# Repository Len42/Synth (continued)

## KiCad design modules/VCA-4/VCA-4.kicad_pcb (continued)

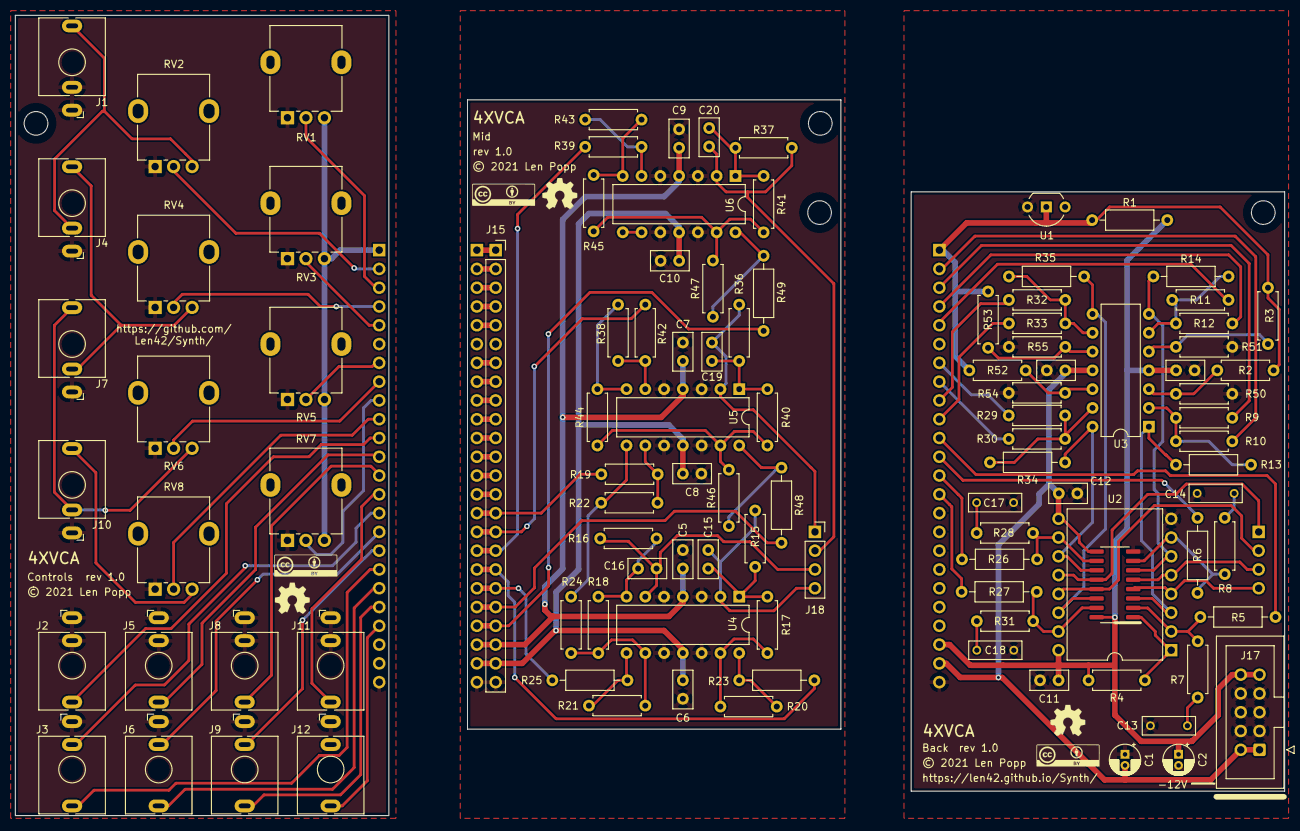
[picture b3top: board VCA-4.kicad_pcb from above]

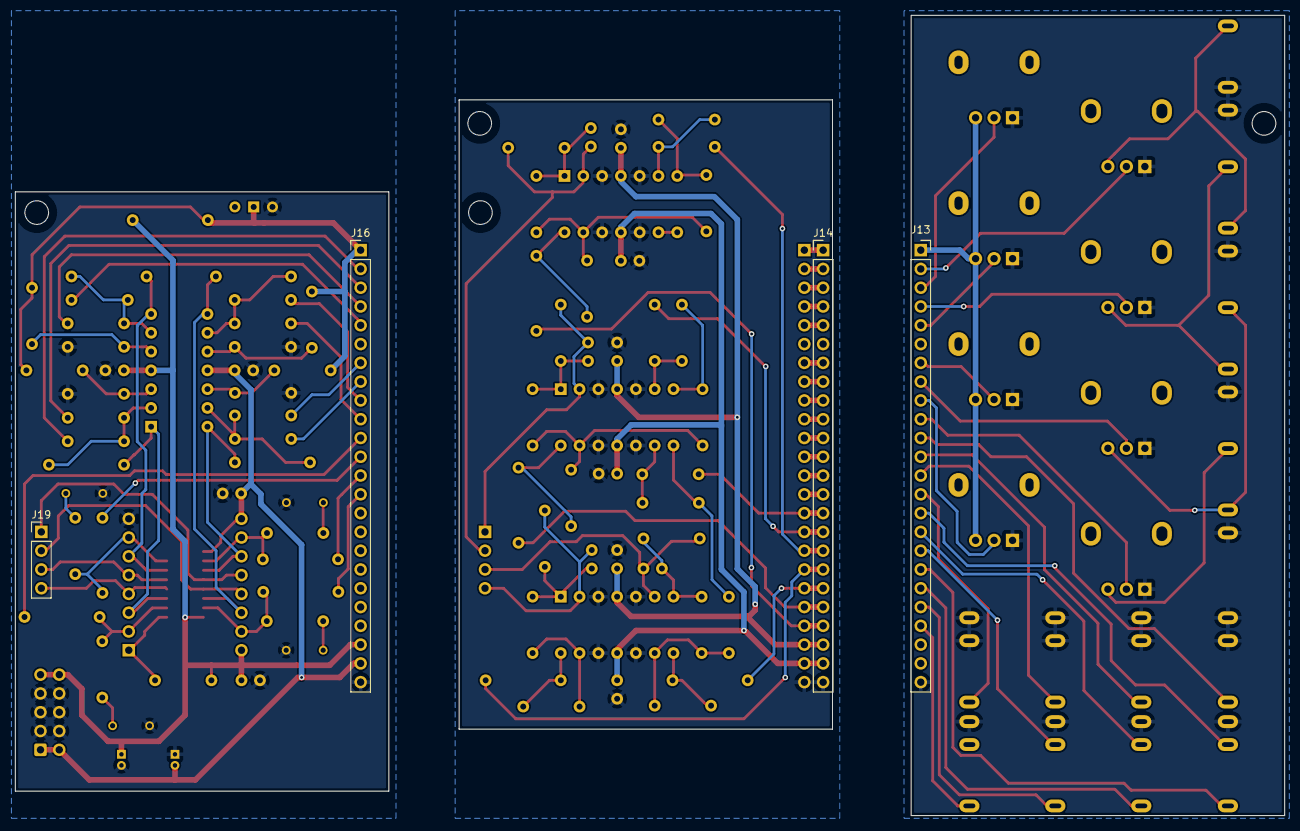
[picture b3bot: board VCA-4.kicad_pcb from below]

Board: 2 copper layers, 171.6 x 108.2 mm, 118 parts (4 on the bottom side), 71 nets.

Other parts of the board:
G2, G2#2, G2#3: Logo_CC_BY
G4, G4#2, G4#3: Logo_OSHW

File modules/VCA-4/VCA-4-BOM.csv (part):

Ref,Qty,Value,Value2,Note,Description,Datasheet,Manufacturer,ManuPartNum,Distributor1,DistributorPartNum1,DistributorPartLink1,Distributor2,DistributorPartNum2,DistributorPartLink2,Distributor3,DistributorPartNum3,DistributorPartLink3
"A1","1","Cable_Eurorack_10","","Length as required","Eurorack 16-10 pin power cable","","","","Thonk","","https://www.thonk.co.uk/shop/eurorack-power-cables/","SynthCube","","https://synthcube.com/cart/eurorack-ribbon-power-cables","Modular Addict","","https://modularaddict.com/parts/eurorack-power-cables-1"
"C1 C2","2","10U","25 VDC","12 V decoupling","Capacitor - Electrolytic - 12 V decoupling","https://industrial.panasonic.com/cdbs/www-data/pdf/RDF0000/A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","Panasonic","EEA-FC1E100","Mouser","667-EEA-FC1E100","https://www.mouser.ca/ProductDetail/Panasonic/EEA-FC1E100?qs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","","","","","",""
"C3 C4 C5 C6 C7 C8 C9 C10 C11 C12","10","100N","","IC decoupling","Capacitor - Ceramic - IC decoupling","https://product.tdk.com/system/files/dam/doc/product/capacit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","TDK","FG18X7R1H104KNT06","Mouser","810-FG18X7R1H104KNT6","https://www.mouser.ca/ProductDetail/810-FG18X7R1H104KNT6","","","","","",""
"C13 C14 C17 C18","4","1N2","","C0G or film","Capacitor - Ceramic","https://www.mouser.ca/datasheet/2/212/1/KEM_F3101_R82-1103738.pdf","Kemet","R82EC1120DQ50J","Mouser","80-R82EC1120DQ50J","https://www.mouser.ca/ProductDetail/KEMET/R82EC1120DQ50J?qs=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","","","","","",""
"C15 C16 C19 C20","4","100P","","","Capacitor - Ceramic","https://www.mouser.ca/datasheet/2/427/VISH_S_A0012659393_1-2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","Vishay","K101J15C0GF53L2","Mouser","594-K101J15C0GF53L2","https://www.mouser.ca/ProductDetail/594-K101J15C0GF53L2","","","","","",""
"H1 H5 H6 H10","4","Screw_M3x0.50x6","","","Machine screw, M3x0.50x6","","","","","","","","","","","",""
"H3 H8","2","Standoff_F-F_11mm_M3x0.50","","","Standoff, 11mm, female-female, M3x0.50","https://www.thonk.co.uk/wp-content/uploads/2018/05/standoff-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","Ettinger","05.03.111","Thonk","Mech_11mm_Standoff_(x10)","https://www.thonk.co.uk/shop/standoffs/","Mouser","710-970110321","https://www.mouser.ca/ProductDetail/Wurth-Elektronik/9701103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","","",""
"J1 J2 J3 J4 J5 J6 J7 J8 J9 J10 J11 J12","12","WQP-PJ398","","","Audio Jack, 2 Poles (Mono / TS), Switched T Pole (Normalling), QingPu / Thonkiconn","http://www.qingpu-electronics.com/en/products/WQP-PJ398SM-362.html","QingPu / Thonk","PJ398SM / WQP518MA","Thonk","PJ398SM","https://www.thonk.co.uk/shop/thonkiconn/","SynthCube","WQP518MA","https://synthcube.com/cart/3-5mm-euro-jacks","Adafruit","4031","https://www.adafruit.com/product/4031"
"J13 J15","2","Conn_Socket_24","","","Generic connector, single row, 01x24, script generated (kicad-library-utils/schlib/autogen/connector/)","https://www.mouser.ca/datasheet/2/445/61303211821-1717799.pdf","","","Adafruit","598","https://www.adafruit.com/product/598","Mouser","710-61303211821","https://www.mouser.ca/ProductDetail/Wurth-Elektronik/6130321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","","",""
"J14 J16","2","Conn_Header_24","","","Generic connector, single row, 01x24, script generated (kicad-library-utils/schlib/autogen/connector/)","https://www.amphenol-icc.com/media/wysiwyg/files/documentati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","","","Adafruit","392","https://www.adafruit.com/product/392","Mouser","649-1012937893601BLF","https://www.mouser.ca/ProductDetail/649-1012937893601BLF","","",""
"J17","1","Conn_Eurorack_10","","","Eurorack 10-pin board power connector","https://www.mouser.ca/datasheet/2/445/61201021621-1717731.pdf","Wurth Elektronik","61201021621","Mouser","710-61201021621","https://www.mouser.ca/ProductDetail/Wurth-Elektronik/6120102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","Mouser","523-G821EU210AAL10Y","https://www.mouser.ca/ProductDetail/523-G821EU210AAL10Y","","",""
"J18","1","Conn_Socket_4","","","Generic connector, single row, 01x04, script generated (kicad-library-utils/schlib/autogen/connector/)","https://www.mouser.ca/datasheet/2/445/61303211821-1717799.pdf","","","Adafruit","598","https://www.adafruit.com/product/598","Mouser","710-61303211821","https://www.mouser.ca/ProductDetail/Wurth-Elektronik/6130321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","","",""
"J19","1","Conn_Header_4","","","Generic connector, single row, 01x04, script generated (kicad-library-utils/schlib/autogen/connector/)","https://www.amphenol-icc.com/media/wysiwyg/files/documentati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","","","Adafruit","392","https://www.adafruit.com/product/392","Mouser","649-1012937893601BLF","https://www.mouser.ca/ProductDetail/649-1012937893601BLF","","",""
"R1 R23 R25 R48 R49","5","1K","5%, 1/4 W","Output limiting","Resistor","https://www.mouser.ca/datasheet/2/427/ccf07-1762725.pdf","Vishay / Dale","CCF071K00JKE36","Mouser","71-CCF071K00JKE36","https://www.mouser.ca/ProductDetail/Vishay-Dale/CCF071K00JKE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","","","","","",""
"R2 R3 R52 R53","4","25K5","1%, 1/6 W","","Resistor","https://www.mouser.ca/datasheet/2/447/Yageo_LR_MFR_1-1714151.pdf","YAGEO","MFR-25FRF52-25K5","Mouser","603-MFR-25FRF52-25K5","https://www.mouser.ca/ProductDetail/603-MFR-25FRF52-25K5","","","","","",""
"R4","1","12K","1%, 1/6 W","","Resistor","https://www.mouser.ca/datasheet/2/447/Yageo_LR_MFR_1-1714151.pdf","YAGEO","MFR-12FTF52-12K","Mouser","603-MFR-12FTF52-12K","https://www.mouser.ca/ProductDetail/603-MFR-12FTF52-12K","","","","","",""
"R5 R6 R26 R27","4","49K9","","","Resistor","https://www.mouser.ca/datasheet/2/427/cmfmil-1762972.pdf","Vishay / Dale","RN55D4992FB14","Mouser","71-RN55D-F-49.9K","https://www.mouser.ca/ProductDetail/?qs=Bfn3yGQ%252BnqpBsi5J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","","","","","",""
"R7 R8 R28 R31","4","220R","1%, 1/6 W","","Resistor","https://www.mouser.ca/datasheet/2/447/Yageo_LR_MFR_1-1714151.pdf","YAGEO","MFR-12FTF52-220R","Mouser"," 603-MFR-12FTF52-220R","https://www.mouser.ca/ProductDetail/603-MFR-12FTF52-220R","","","","","",""
"R9 R11 R29 R32","4","75K","1%, 1/6 W","","Resistor","https://www.mouser.ca/datasheet/2/447/Yageo_LR_MFR_1-1714151.pdf","YAGEO","MFR-12FTF52-75K","Mouser","603-MFR-12FTF52-75K","https://www.mouser.ca/ProductDetail/YAGEO/MFR-12FTF52-75K?qs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","","","","","",""
"R10 R12 R30 R33","4","150K","1%, 1/6 W","","Resistor","https://www.mouser.ca/datasheet/2/447/Yageo_LR_MFR_1-1714151.pdf","YAGEO","MFR-12FTF52-150K","Mouser","603-MFR-12FTF52-150K","https://www.mouser.ca/ProductDetail/YAGEO/MFR-12FTF52-150K?q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","","","","","",""
"R13 R14 R34 R35","4","60K1","1%","","Resistor","https://www.mouser.ca/datasheet/2/427/cmfmil-1762972.pdf","Vishay / Dale","RN55D6012FB14","Mouser","71-RN55D-F-60.1K","https://www.mouser.ca/ProductDetail/71-RN55D-F-60.1K","","","","","",""
"R15 R16 R36 R37","4","20K","1%, 1/6 W","","Resistor","https://www.mouser.ca/datasheet/2/447/Yageo_LR_MFR_1-1714151.pdf","YAGEO","MFR-12FTF52-20K","Mouser","603-MFR-12FTF52-20K","https://www.mouser.ca/ProductDetail/YAGEO/MFR-12FTF52-20K?qs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","","","","","",""
"R17 R18 R19 R20 R21 R22 R24 R38 R39 R40 R41 R42 R43 R44 R45 R46 R47","17","47K","1%, 1/6 W","","Resistor","https://www.mouser.ca/datasheet/2/447/Yageo_LR_MFR_1-1714151.pdf","YAGEO","MFR-12FTF52-47K","Mouser","603-MFR-12FTF52-47K","https://www.mouser.ca/ProductDetail/YAGEO/MFR-12FTF52-47K?qs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","","","","","",""
"R50 R51 R54 R55","4","11K","1%, 1/6 W","","Resistor","https://www.mouser.ca/datasheet/2/447/Yageo_LR_MFR_1-1714151.pdf","YAGEO","MFR-12FTF52-11K","Mouser","603-MFR-12FTF52-11K","https://www.mouser.ca/ProductDetail/YAGEO/MFR-12FTF52-11K?qs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","","","","","",""
"RV1 RV3 RV5 RV7","4","100K","LIN","","Potentiometer","https://www.mouser.ca/datasheet/2/13/alpha_taiwan_08192019_R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","Alpha","RD901F-40-15R1-B100K-00DL1","Thonk","Group_Pot_Alpha_6.35mm","https://www.thonk.co.uk/shop/alpha-9mm-pots/","Mouser","311-1940F-15R1-B100K","https://www.mouser.ca/ProductDetail/Alpha-Taiwan/RD901F-40-1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","SynthCube","9MMALPHAPOTMSTR","https://synthcube.com/cart/alpha-9mm-potentiometer-right-ang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"
"RV2 RV4 RV6 RV8","4","100K","LIN","","Potentiometer","http://www.song-huei.com/proimages//eng/pdfimages/R0904N.pdf","Song Huei","R0904N*","SynthCube","SH9MMTPOTMSTR","https://synthcube.com/cart/9mm-trimmer-pots","Thonk","Group_SongHuei_TTP","https://www.thonk.co.uk/shop/ttpots/","","",""
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
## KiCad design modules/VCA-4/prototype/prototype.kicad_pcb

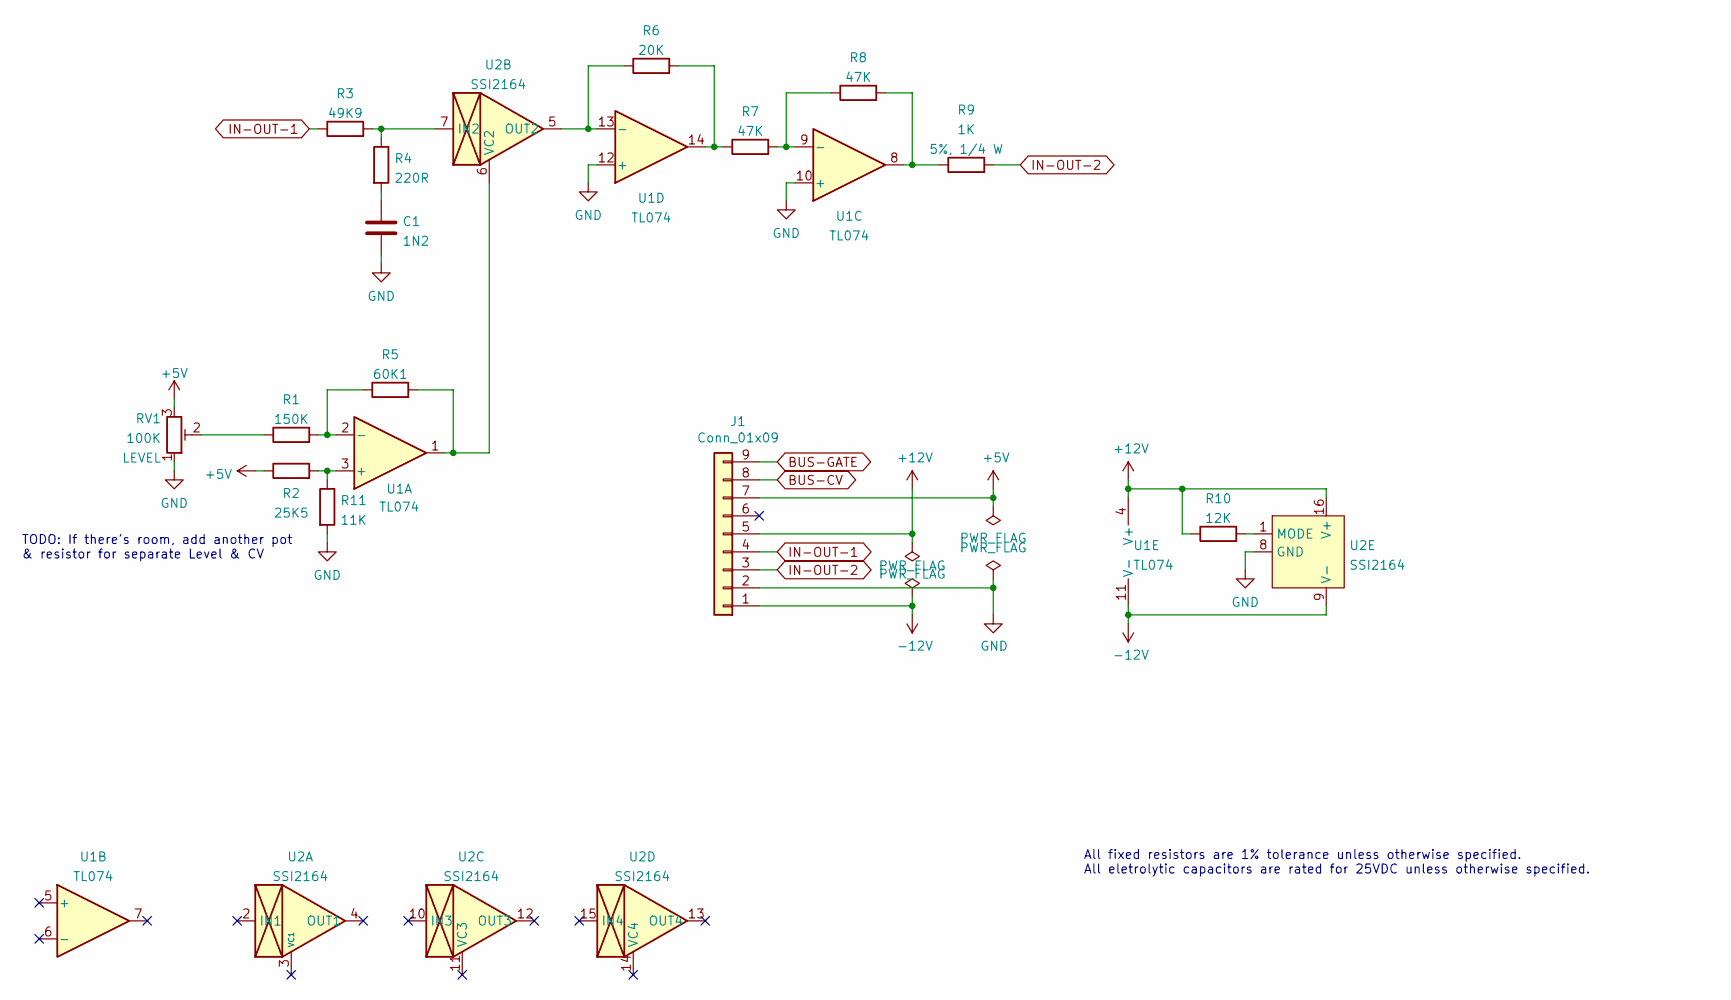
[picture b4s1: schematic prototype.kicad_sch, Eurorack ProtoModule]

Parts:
C1: 1N2; C_Rect_Kemet_L7.2mm_W2.5mm_P5mm
J1: Conn_01x09; PinHeader_1x09_P2.54mm_Vertical
R1: 150K; R_Axial_DIN0207_L6.3mm_D2.5mm_P7.62mm_Horizontal; ManufacturerPartNum MFR-12*
R2: 25K5; R_Axial_DIN0207_L6.3mm_D2.5mm_P7.62mm_Horizontal; ManufacturerPartNum MFR-12*
R3: 49K9; R_Axial_DIN0207_L6.3mm_D2.5mm_P10.16mm_Horizontal; ManufacturerPartNum MFR-12*
R4: 220R; R_Axial_DIN0207_L6.3mm_D2.5mm_P7.62mm_Horizontal; ManufacturerPartNum MFR-12*
R5: 60K1; SB_Gen_1; ManufacturerPartNum MFR-12*
R6: 20K; SB_Gen_1; ManufacturerPartNum MFR-12*
R7: 47K; SB_Gen_5; ManufacturerPartNum MFR-12*
R8: 47K; SB_Gen_1; ManufacturerPartNum MFR-12*
R9: 1K; SB_Gen_1; ManufacturerPartNum CCF071K00JKE36
R10: 12K; R_Axial_DIN0207_L6.3mm_D2.5mm_P7.62mm_Horizontal; ManufacturerPartNum MFR-12*
R11: 11K; SB_Gen_1; ManufacturerPartNum MFR-12*
RV1: 100K; Potentiometer_Bourns_3310R_Top; ManufacturerPartNum 3386*
U1: TL074; DIP-14_W7.62mm; ManufacturerPartNum TL074BCN
U2: SSI2164; Breakout_DIP-16_W15.24mm; ManufacturerPartNum SSI2164

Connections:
+5V: J1.7, R2.1, RV1.3
+12V: J1.5, R10.1, U1.4 (V+), U2.16 (V+)
-12V: J1.1, U1.11 (V-), U2.9 (V-)
BUS-CV: J1.8
BUS-GATE: J1.9
GND: C1.2, J1.2, R11.2, RV1.1, U1.10 (+), U1.12 (+), U2.8 (GND)
IN-OUT-1: J1.4, R3.1
IN-OUT-2: J1.3, R9.2
unnamed: C1.1, R4.2
unnamed: R1.1, RV1.2
unnamed: R1.2, R5.1, U1.2 (-)
unnamed: R3.2, R4.1, U2.7 (IN2)
unnamed: R5.2, U1.1, U2.6 (VC2)
unnamed: R6.1, U1.13 (-), U2.5 (OUT2)
unnamed: R6.2, R7.1, U1.14
unnamed: R7.2, R8.1, U1.9 (-)
unnamed: R8.2, R9.1, U1.8
unnamed: R10.2, U2.1 (MODE)
unnamed: R2.2, R11.1, U1.3 (+)

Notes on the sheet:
TODO: If there's room, add another pot & resistor for separate Level & CV
All fixed resistors are 1% tolerance unless otherwise specified. All eletrolytic capacitors are rated for 25VDC unless otherwise specified.

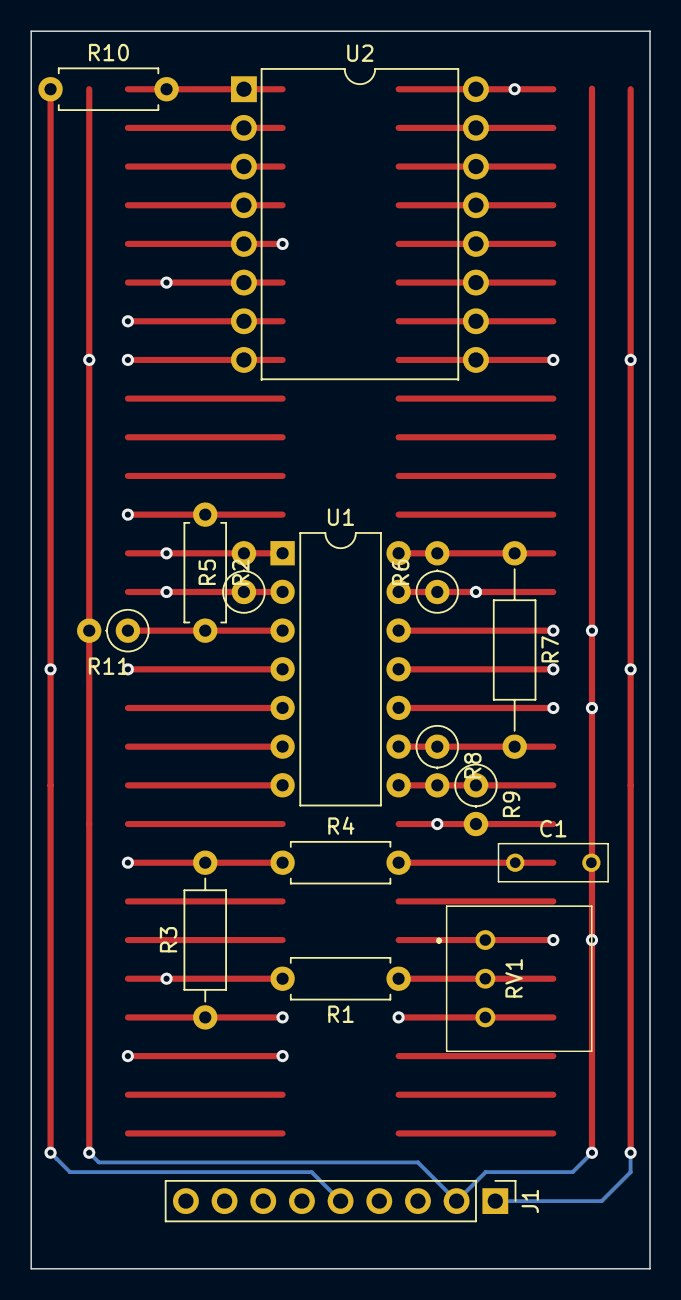
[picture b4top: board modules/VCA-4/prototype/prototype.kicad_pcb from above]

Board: 6 copper layers, 40.6 x 81.3 mm, 16 parts (0 on the bottom side), 17 nets.

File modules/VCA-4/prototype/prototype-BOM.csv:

Ref,Qty,Name,Value,Value2,Note,Description,Datasheet,Manufacturer,ManuPartNum,Distributor1,DistributorPartNum1,DistributorPartLink1,Distributor2,DistributorPartNum2,DistributorPartLink2
"C1","1","CF","1N2","","","Capacitor - Film","","","","","","","","",""
"J1","1","Conn_01x09","Conn_01x09","","","Generic connector, single row, 01x09, script generated (kicad-library-utils/schlib/autogen/connector/)","","","","","","","","",""
"R1","1","R","150K","1%, 1/6 W","","Resistor","https://www.mouser.ca/datasheet/2/447/Yageo_LR_MFR_1-1714151.pdf","YAGEO","MFR-12*","Mouser","603-MFR-12*","https://www.mouser.ca/c/passive-components/resistors/film-re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","","",""
"R2","1","R","25K5","1%, 1/6 W","","Resistor","https://www.mouser.ca/datasheet/2/447/Yageo_LR_MFR_1-1714151.pdf","YAGEO","MFR-12*","Mouser","603-MFR-12*","https://www.mouser.ca/c/passive-components/resistors/film-re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","","",""
"R3","1","R","49K9","1%, 1/6 W","","Resistor","https://www.mouser.ca/datasheet/2/447/Yageo_LR_MFR_1-1714151.pdf","YAGEO","MFR-12*","Mouser","603-MFR-12*","https://www.mouser.ca/c/passive-components/resistors/film-re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","","",""
"R4","1","R","220R","1%, 1/6 W","","Resistor","https://www.mouser.ca/datasheet/2/447/Yageo_LR_MFR_1-1714151.pdf","YAGEO","MFR-12*","Mouser","603-MFR-12*","https://www.mouser.ca/c/passive-components/resistors/film-re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","","",""
"R5","1","R","60K1","1%, 1/6 W","","Resistor","https://www.mouser.ca/datasheet/2/447/Yageo_LR_MFR_1-1714151.pdf","YAGEO","MFR-12*","Mouser","603-MFR-12*","https://www.mouser.ca/c/passive-components/resistors/film-re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","","",""
"R6","1","R","20K","1%, 1/6 W","","Resistor","https://www.mouser.ca/datasheet/2/447/Yageo_LR_MFR_1-1714151.pdf","YAGEO","MFR-12*","Mouser","603-MFR-12*","https://www.mouser.ca/c/passive-components/resistors/film-re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","","",""
"R7 R8","2","R","47K","1%, 1/6 W","","Resistor","https://www.mouser.ca/datasheet/2/447/Yageo_LR_MFR_1-1714151.pdf","YAGEO","MFR-12*","Mouser","603-MFR-12*","https://www.mouser.ca/c/passive-components/resistors/film-re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","","",""
"R9","1","R_1K_Output","1K","5%, 1/4 W","Output limiting","Resistor","https://www.mouser.ca/datasheet/2/427/ccf07-1762725.pdf","Vishay / Dale","CCF071K00JKE36","Mouser","71-CCF071K00JKE36","https://www.mouser.ca/ProductDetail/Vishay-Dale/CCF071K00JKE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","","",""
"R10","1","R","12K","1%, 1/6 W","","Resistor","https://www.mouser.ca/datasheet/2/447/Yageo_LR_MFR_1-1714151.pdf","YAGEO","MFR-12*","Mouser","603-MFR-12*","https://www.mouser.ca/c/passive-components/resistors/film-re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","","",""
"RV1","1","R_POT_TRIM","100K","","","Trim-potentiometer","https://www.mouser.ca/datasheet/2/54/3386-776606.pdf","Bourns","3386*","Mouser","652-3386*","https://www.mouser.ca/c/passive-components/resistors/variabl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","","",""
"U1","1","TL074","TL074","","","Quad Low-Noise JFET-Input Operational Amplifiers, DIP-14/SOIC-14","http://www.ti.com/lit/ds/symlink/tl071.pdf","Texas Instruments","TL074BCN","Mouser","595-TL074BCN","https://www.mouser.ca/ProductDetail/?qs=vxEfx8VrU7BHurOY5iQd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","","",""
"U2","1","SSI2164","SSI2164","","","Fatkeys™ Quad Voltage Controlled Amplifier","http://soundsemiconductor.com/downloads/ssi2164datasheet.pdf","Sound Semiconductor","SSI2164","Synthcube","ICNSSI2164SMT","https://synthcube.com/cart/sound-semiconductor-ssi2164-fatke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","Antique Electronic Supply","P-Q-SSI2164","https://www.tubesandmore.com/products/integrated-circuit-ssi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"

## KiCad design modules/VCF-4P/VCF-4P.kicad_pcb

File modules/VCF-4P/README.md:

# Four-Pole VCF

## 10HP Eurorack Module

_A low-pass filter using the SSI2140 chip_

### Features
- Four-pole, 24 db/octave low-pass filter made with an [SSI2140 IC](https://soundsemiconductor.com/downloads/ssi2140datasheet.pdf)
- Self-oscillates at maximum resonance
- Two CV inputs for cutoff frequency. One is 1V/octave and the other has an input attenuator.
- 1V/octave input can default to the Eurorack bus CV line (jumper-selectable) - more info [here](https://lenp.net/synth/eurorack-bus-cv-gate.html)
- Resonance CV input with attenuator
- A large knob

### Notes
The cutoff CV inputs can be trimmed to track 1V/octave pretty well (but not as accurately as a VCO). Due to variations between different SSI2140 chips, it may be necessary to change the value of R31 to get proper scaling. If you don't care about precise volt/octave scaling, just set the trim pots RV9 & RV10 somewhere near the middle, or even replace them with fixed 4.7 kΩ resistors.

The SSI2140 VCF chip comes in an SSOP package that I cannot solder, but fortunately it's also available pre-soldered to a breakout board - that's what I use here.

The filter capacitors C8-C11 are specified as high-stability types. Traditionally, polystyrene caps would be used, but those are hard to come by these days (hardly anyone makes them any more) so I've chosen PPS film caps. Ordinary polyester film caps might be OK, or audio-grade ceramics (C0G/NP0 type).

This module requires a 16-pin Eurorack power cable, but it does not depend on +5V power from the Eurorack system.

PCB layouts are provided in KiCad and gerber formats. A front panel design is included as a drilled PCB layout (with no labels or graphics).

The PCBs that I used can be ordered from OSH Park. The designs are here:
- [Front panel](https://oshpark.com/shared_projects/uQCignas)
- [Controls board](https://oshpark.com/shared_projects/4RLSW85r)
- [Main board](https://oshpark.com/shared_projects/U6pC6p9E)

Please note that I am a hobbyist, not a trained electronics engineer. No guarantees!

### Software Used

* [KiCad](https://www.kicad.org/) 6.0.6

<hr /><div><div style="float:left; padding-right:10px;"></div><div style="xfloat:left; padding-left:10px;"><br />© 2022 Len Popp CC BY<br />This work is licensed under a <a rel="license" href="http://creativecommons.org/licenses/by/4.0/">Creative Commons Attribution 4.0 International License</a>.</div></div>

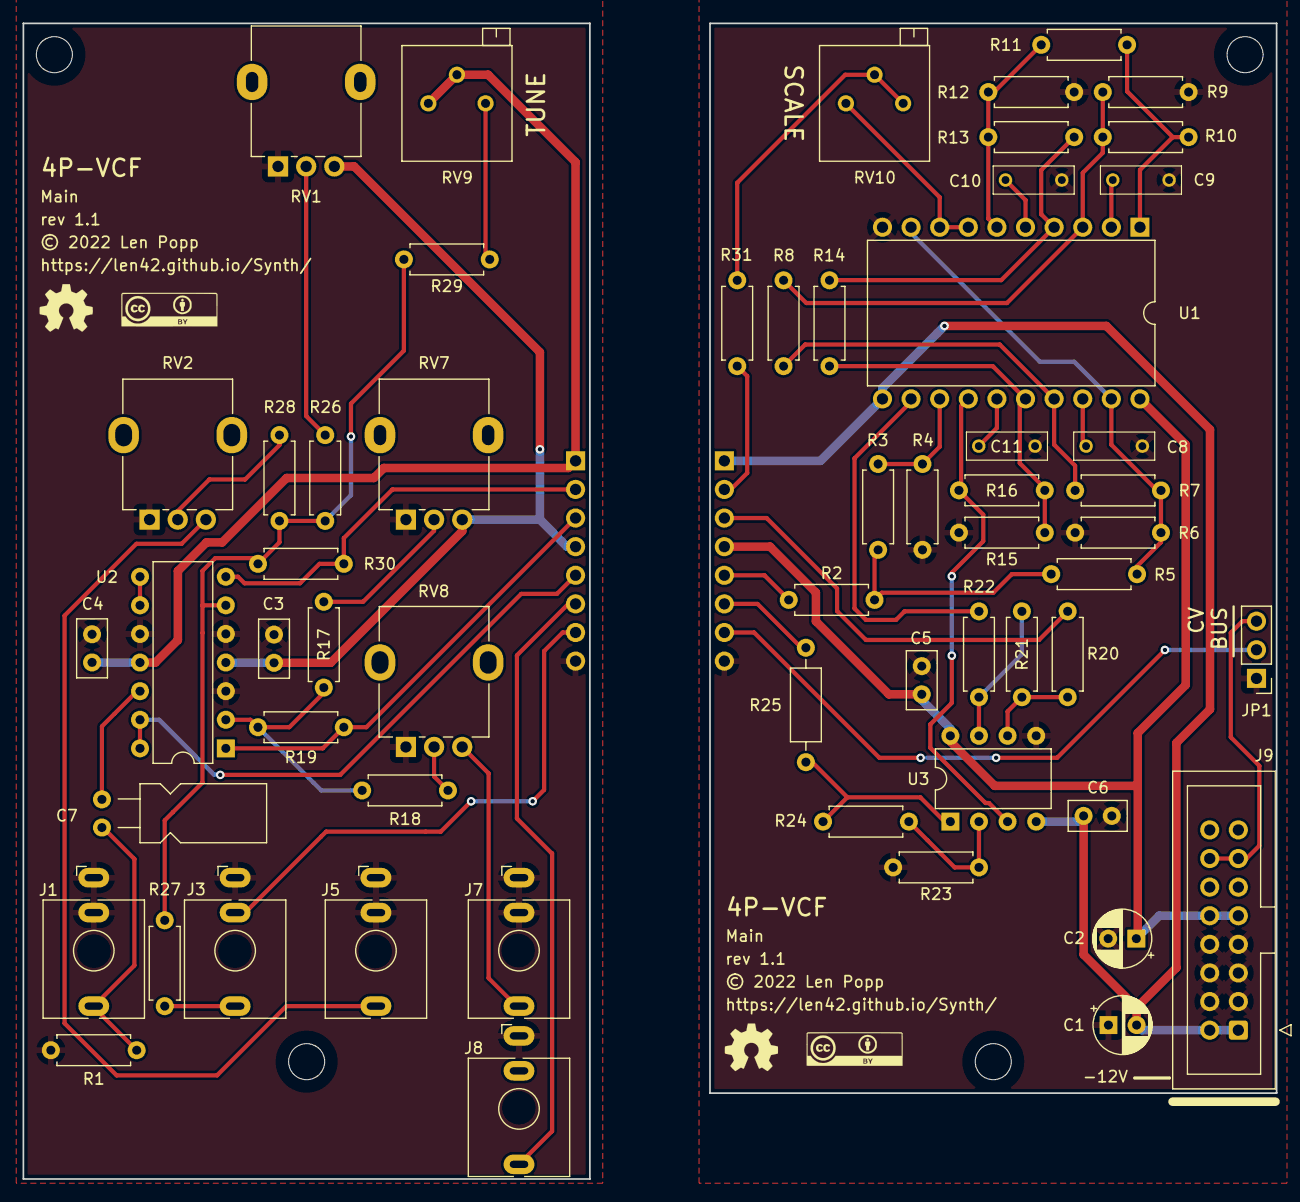
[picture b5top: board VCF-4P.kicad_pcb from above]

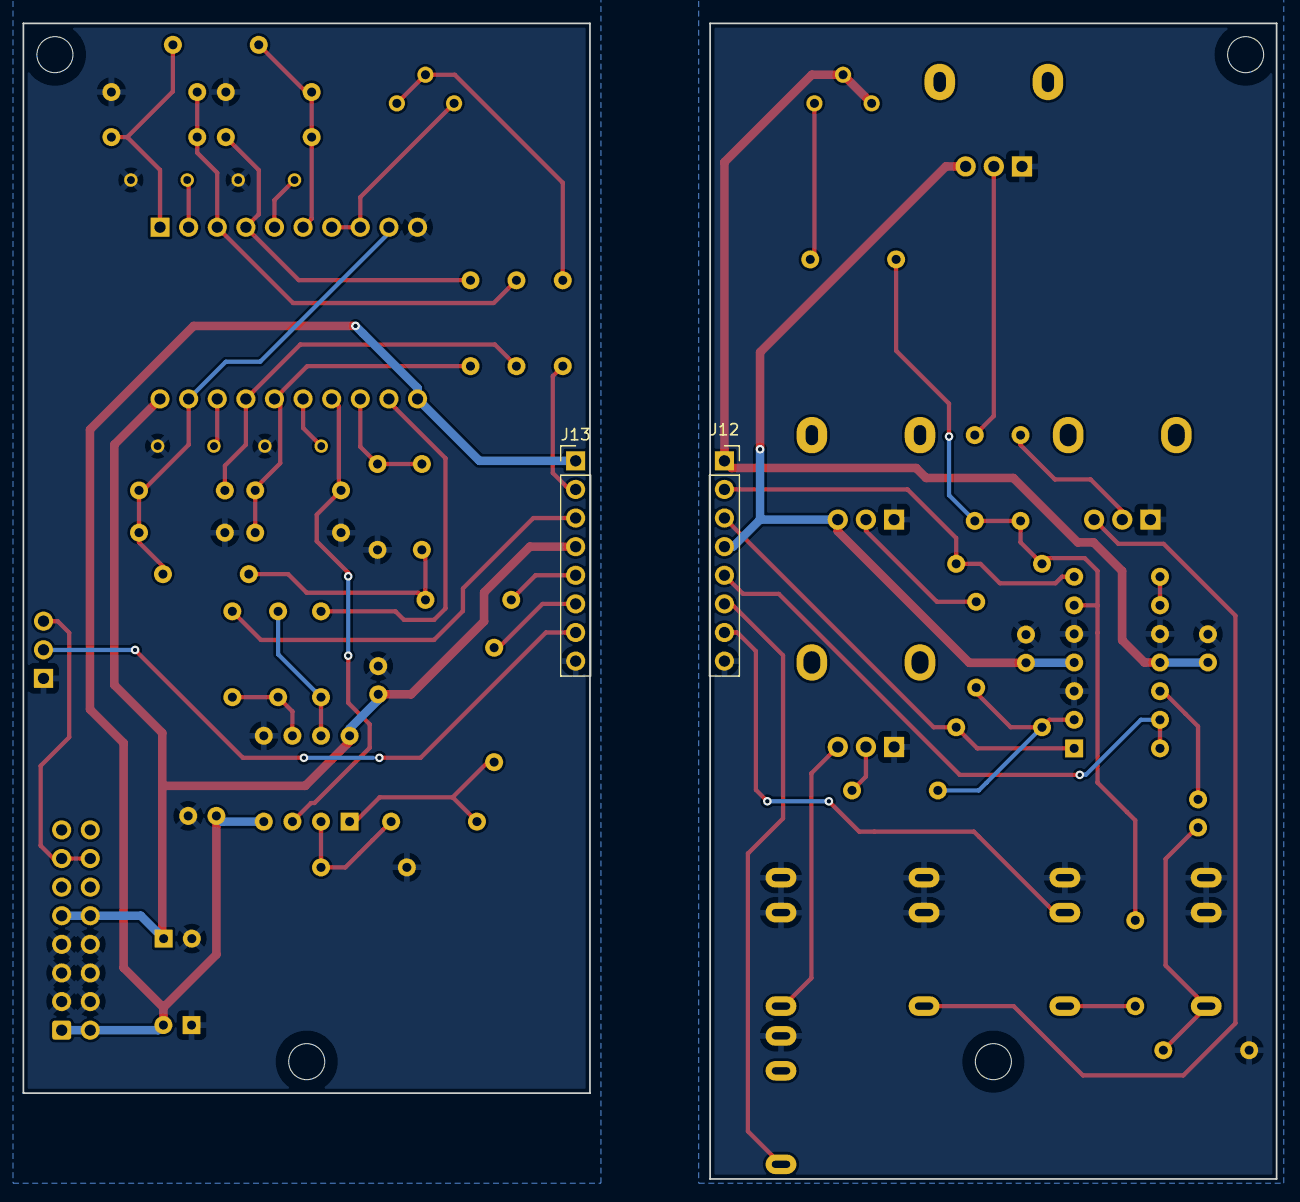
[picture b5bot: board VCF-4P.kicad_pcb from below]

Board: 2 copper layers, 111.3 x 102.6 mm, 68 parts (2 on the bottom side), 43 nets.

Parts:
C1, C2: 10U; CP_Radial_D5.0mm_P2.50mm
C3, C4, C5, C6: 100N; C_Disc_D5.0mm_W2.5mm_P2.50mm
C7: 10U; C_Radial_L11.0mm_D5.0mm_P2.50mm_Horiz
C8, C9, C10, C11: 1N; C_Rect_Kemet_L7.2mm_W2.5mm_P5mm
G1, G1#2: Logo_CC_BY
G3, G3#2: Logo_OSHW
H3, H5, H8, H10: Hole_M3; MountingHole_PCB_3.2mm_M3
J1, J3, J5, J7, J8: WQP-PJ398; Jack_3.5mm_QingPu_WQP-PJ398SM_Vertical
J9: Conn_Eurorack_16; IDC-Header-Eurorack-16-TH
J12: Conn_PCB_Front; PinSocket_1x08_P2.54mm_Vertical
J13: Conn_PCB_Back; PinHeader_1x08_P2.54mm_Vertical
JP1: CV-BUS; PinHeader_1x03_P2.54mm_Vertical
R1, R19, R20, R21, R26, R27, R28, R30: 100K; R_Axial_DIN0207_L6.3mm_D2.5mm_P7.62mm_Horizontal
R2: 36K; R_Axial_DIN0207_L6.3mm_D2.5mm_P7.62mm_Horizontal
R3: 24K; R_Axial_DIN0207_L6.3mm_D2.5mm_P7.62mm_Horizontal
R4: 1K; R_Axial_DIN0207_L6.3mm_D2.5mm_P7.62mm_Horizontal
R5, R7, R8, R10, R11, R13, R14, R16: 10K; R_Axial_DIN0207_L6.3mm_D2.5mm_P7.62mm_Horizontal
R6, R9, R12, R15: 200R; R_Axial_DIN0207_L6.3mm_D2.5mm_P7.62mm_Horizontal
R17: 240K; R_Axial_DIN0207_L6.3mm_D2.5mm_P7.62mm_Horizontal
R18: 200K; R_Axial_DIN0207_L6.3mm_D2.5mm_P7.62mm_Horizontal
R22: 20K; R_Axial_DIN0207_L6.3mm_D2.5mm_P7.62mm_Horizontal
R23: 30K; R_Axial_DIN0207_L6.3mm_D2.5mm_P7.62mm_Horizontal
R24, R29: 160K; R_Axial_DIN0207_L6.3mm_D2.5mm_P7.62mm_Horizontal
R25: 1K; R_Axial_DIN0207_L6.3mm_D2.5mm_P10.16mm_Horizontal
R31: 33K; R_Axial_DIN0207_L6.3mm_D2.5mm_P7.62mm_Horizontal
RV1, RV7: 100K; Potentiometer_Alpha_RD901F-40-00D_Single_Vertical
RV2, RV8: 100K; Potentiometer_SongHuei_Single_Vertical
RV9, RV10: 10K; Potentiometer_Bourns_3296P_Horizontal
U1: SSI2140; Breakout_DIP-20_W15.24mm
U2: TL074; DIP-14_W7.62mm
U3: TL072; DIP-8_W7.62mm

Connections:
+12V: C2.1, C3.1, C5.1, J9.9 (+12V), J9.10, J12.4, J13.4, RV1.3, RV7.3, U1.20 (V+), U2.4 (V+), U3.8 (V+)
-12V: C1.2, C4.2, C6.2, J9.1 (-12V), J9.2, J12.1, J13.1, RV9.2, RV9.3, U1.11 (V-), U2.11 (V-), U3.4 (V-)
CV-BUS: J3.TN, J12.7, J13.7, JP1.2 (C)
CV-FREQ-1VOCT: J3.T, R27.1
CV-FREQ-BUF: J12.2, J13.2, R30.2, R31.1, U2.7
CV-FREQ-MOD-ATTEN: R28.1, RV2.2
CV-FREQ-POT: R26.1, RV1.2
CV-RES-BUF: J12.3, J13.3, R19.2, R20.1, U2.1
CV-RES-MOD-ATTEN: R18.1, RV8.2
CV-RES-POT: R17.1, RV7.2
GND: C1.1, C2.2, C3.2, C4.1, C5.2, C6.1, C8.2, C9.2, C10.2, C11.2, J1.S, J1.TN, J3.S, J5.S, J5.TN, J7.S, J7.TN, J8.S, J9.3 (GND), J9.4, J9.5 (GND), J9.6, J9.7 (GND), J9.8, J12.8, J13.8, JP1.1 (A), R1.2, R4.2, R6.2, R9.2, R12.2, R15.2, R23.2, RV1.1, RV2.1, RV7.1, RV8.1, U1.10 (GND), U2.3 (+), U2.5 (+), U2.10 (+), U3.5 (+)
IN-AUDIO: C7.1, J1.T, R1.1
IN-AUDIO-BUF: J12.5, J13.5, R2.1, U2.13 (-), U2.14
unnamed: C7.2, U2.12 (+)
unnamed: C8.1, U1.18 (CAP)
unnamed: C9.1, U1.2 (CAP)
unnamed: C10.1, U1.5 (CAP)
unnamed: C11.1, U1.15 (CAP)
unnamed: J5.T, RV2.3
unnamed: J7.T, RV8.3
unnamed: J9.13 (CV), J9.14, JP1.3 (B)
unnamed: R2.2, R3.1, R5.1
unnamed: R3.2, R4.1, U1.13 (IN+)
unnamed: R5.2, R6.1, R7.1, U1.9 (OUT), U1.19 (IN)
unnamed: R7.2, R8.1, U1.17 (OUT)
unnamed: R8.2, R9.1, R10.1, U1.3 (IN)
unnamed: R10.2, R11.1, U1.1 (OUT)
unnamed: R11.2, R12.1, R13.1, U1.6 (IN)
unnamed: R13.2, R14.1, U1.4 (OUT)
unnamed: R14.2, R15.1, R16.1, U1.16 (IN)
unnamed: R16.2, U1.14 (OUT), U3.3 (+)
unnamed: R17.2, R18.2, R19.1, U2.2 (-)
unnamed: R20.2, R21.1, U3.6 (-)
unnamed: R21.2, R22.1, U3.7
unnamed: R22.2, U1.12 (Q-CTRL)
unnamed: R23.1, R24.1, U3.2 (-)
unnamed: R24.2, R25.1, U3.1
unnamed: R26.2, R27.2, R28.2, R29.2, R30.1, U2.6 (-)
unnamed: R29.1, RV9.1
unnamed: R31.2, RV10.1, RV10.2
unnamed: RV10.3, U1.7 (EXPO-CTRL), U1.8 (TEMPCO)
unnamed: U2.8, U2.9 (-)
OUT-AUDIO: J8.T, J12.6, J13.6, R25.2

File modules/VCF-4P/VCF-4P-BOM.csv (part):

Ref,Qty,Value,Value2,Note,Description,Datasheet,Manufacturer,ManuPartNum,Distributor1,DistributorPartNum1,DistributorPartLink1,Distributor2,DistributorPartNum2,DistributorPartLink2,Distributor3,DistributorPartNum3,DistributorPartLink3
"A1","1","Cable_Eurorack_16","","Length as required","Eurorack 16-16 pin power & bus cable","","","","Thonk","","https://www.thonk.co.uk/shop/eurorack-power-cables/","SynthCube","","https://synthcube.com/cart/eurorack-ribbon-power-cables","Modular Addict","","https://modularaddict.com/parts/eurorack-power-cables-1"
"C1 C2","2","10U","","12 V decoupling","Capacitor - Electrolytic - 12 V decoupling","https://www.mouser.ca/datasheet/2/315/ABA0000C1059-947582.pdf","Panasonic","ECE-A1VKS100I","Mouser","667-ECE-A1VKS100I","https://www.mouser.ca/ProductDetail/667-ECE-A1VKS100I","Thonk","","https://www.thonk.co.uk/shop/eurorack-diy-essentials/","","",""
"C3 C4 C5 C6","4","100N","","IC decoupling","Capacitor - Ceramic - IC decoupling","https://product.tdk.com/system/files/dam/doc/product/capacit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","TDK","FG18X7R1H104KNT06","Mouser","810-FG18X7R1H104KNT6","https://www.mouser.ca/ProductDetail/810-FG18X7R1H104KNT6","","","","","",""
"C7","1","10U","","Non-polarized","Capacitor - Non-polarized Electrolytic","https://www.mouser.ca/datasheet/2/315/ABA0000C1053-947510.pdf","Panasonic","ECE-A1EN100UI","Mouser","667-ECE-A1EN100UI","https://www.mouser.ca/ProductDetail/Panasonic/ECE-A1EN100UI?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","","","","","",""
"C8 C9 C10 C11","4","1N","","","Capacitor - Film","https://www.mouser.ca/datasheet/2/212/1/KEM_F3072_SMR-1103375.pdf","KEMET","SMR5102J50J01L16.5CBULK ","Mouser","80-SMR5102J50J0116","https://www.mouser.ca/ProductDetail/?qs=lyRJTFulC0ahcLuVpByx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","","","","","",""
"H1","1","Jumper_2","","","Jumper connector, 2-pin socket","https://www.mouser.ca/datasheet/2/209/KC-301174-1171759.pdf","","","Mouser","151-8013-E","https://www.mouser.ca/ProductDetail/Kobiconn/151-8013-E?qs=R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","Adafruit","3525","https://www.adafruit.com/product/3525","","",""
"H2 H6 H7 H11","4","M3x0.50x6","","","Machine screw, M3x0.50x6","","","","","","","","","","","",""
"H4 H9","2","11mm_M3x0.50","","","Standoff, 11mm, female-female, M3x0.50","https://www.thonk.co.uk/wp-content/uploads/2018/05/standoff-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","Ettinger","05.03.111","Thonk","Mech_11mm_Standoff_(x10)","https://www.thonk.co.uk/shop/standoffs/","Mouser","710-970110321","https://www.mouser.ca/ProductDetail/Wurth-Elektronik/9701103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","Mouser","144-MTS-11","https://www.mouser.ca/ProductDetail/144-MTS-11"
"J1 J3 J5 J7 J8","5","WQP-PJ398","","","Audio Jack, 2 Poles (Mono / TS), Switched T Pole (Normalling), QingPu / Thonkiconn","http://www.qingpu-electronics.com/en/products/WQP-PJ398SM-362.html","QingPu / Thonk","PJ398SM / WQP518MA","Thonk","PJ398SM","https://www.thonk.co.uk/shop/thonkiconn/","SynthCube","WQP518MA","https://synthcube.com/cart/3-5mm-euro-jacks","Adafruit","4031","https://www.adafruit.com/product/4031"
"J9","1","Conn_Eurorack_16","","","Eurorack 16-pin board power/CV/gate bus connector","https://www.mouser.ca/datasheet/2/445/61201621621-1717735.pdf","Wurth Elektronik","61201621621","Mouser","710-61201621621","https://www.mouser.ca/ProductDetail/Wurth-Elektronik/6120162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","","","","","",""
"J12","1","Conn_PCB_Front","","","Generic connector, single row, 01x08, script generated (kicad-library-utils/schlib/autogen/connector/)","","","","Adafruit","598","https://www.adafruit.com/product/598","Mouser","710-61303211821","https://www.mouser.ca/ProductDetail/Wurth-Elektronik/6130321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","","",""
"J13","1","Conn_PCB_Back","","","Generic connector, single row, 01x08, script generated (kicad-library-utils/schlib/autogen/connector/)","","","","Adafruit","392","https://www.adafruit.com/product/392","Mouser","649-1012937893601BLF","https://www.mouser.ca/ProductDetail/649-1012937893601BLF","","",""
"JP1","1","CV-BUS","","","Jumper pins, 3-pole, pins 1+2 closed/bridged","","","","Adafruit","392","https://www.adafruit.com/product/392","Mouser","649-1012937893601BLF","https://www.mouser.ca/ProductDetail/649-1012937893601BLF","","",""
"R1 R19 R20 R21 R26 R27 R28 R30","8","100K","1%, 1/6 W","","Resistor","https://www.mouser.ca/datasheet/2/447/Yageo_LR_MFR_1-1714151.pdf","YAGEO","MFR-12FTF52-100K","Mouser","603-MFR-12FTF52-100K","https://www.mouser.ca/ProductDetail/YAGEO/MFR-12FTF52-100K?q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","","","","","",""
"R2","1","36K","1%, 1/6 W","","Resistor","https://www.mouser.ca/datasheet/2/447/Yageo_LR_MFR_1-1714151.pdf","YAGEO","MFR-12FTF52-36K","Mouser","603-MFR-12FTF52-36K","https://www.mouser.ca/ProductDetail/YAGEO/MFR-12FTF52-36K?qs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","","","","","",""
"R3","1","24K","1%, 1/6 W","","Resistor","https://www.mouser.ca/datasheet/2/447/Yageo_LR_MFR_1-1714151.pdf","YAGEO","MFR-12FTF52-24K","Mouser","603-MFR-12FTF52-24K","https://www.mouser.ca/ProductDetail/YAGEO/MFR-12FTF52-24K?qs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","","","","","",""
"R4","1","1K","1%, 1/6 W","","Resistor","https://www.mouser.ca/datasheet/2/447/Yageo_LR_MFR_1-1714151.pdf","YAGEO","MFR-12FTF52-1K","Mouser","603-MFR-12FTF52-1K","https://www.mouser.ca/ProductDetail/YAGEO/MFR-12FTF52-1K?qs=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","","","","","",""
"R5 R7 R8 R10 R11 R13 R14 R16","8","10K","1%, 1/6 W","","Resistor","https://www.mouser.ca/datasheet/2/447/Yageo_LR_MFR_1-1714151.pdf","YAGEO","MFR-12FRF52-10K","Mouser","603-MFR-12FRF5210K","https://www.mouser.ca/ProductDetail/YAGEO/MFR-12FRF52-10K?qs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","","","","","",""
"R6 R9 R12 R15","4","200R","1%, 1/6 W","","Resistor","https://www.mouser.ca/datasheet/2/447/Yageo_LR_MFR_1-1714151.pdf","YAGEO","MFR-12FTF52-200R","Mouser","603-MFR-12FTF52-200R","https://www.mouser.ca/ProductDetail/YAGEO/MFR-12FTF52-200R?q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","","","","","",""
"R17","1","240K","1%, 1/6 W","","Resistor","https://www.mouser.ca/datasheet/2/447/Yageo_LR_MFR_1-1714151.pdf","YAGEO","MFR-12FTF52-240K","Mouser","603-MFR-12FTF52-240K","https://www.mouser.ca/ProductDetail/YAGEO/MFR-12FTF52-240K?q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","","","","","",""
"R18","1","200K","1%, 1/6 W","","Resistor","https://www.mouser.ca/datasheet/2/447/Yageo_LR_MFR_1-1714151.pdf","YAGEO","MFR-12FTF52-200K","Mouser","603-MFR-12FTF52-200K","https://www.mouser.ca/ProductDetail/YAGEO/MFR-12FTF52-200K?q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","","","","","",""
"R22","1","20K","1%, 1/6 W","","Resistor","https://www.mouser.ca/datasheet/2/447/Yageo_LR_MFR_1-1714151.pdf","YAGEO","MFR-12FTF52-20K","Mouser","603-MFR-12FTF52-20K","https://www.mouser.ca/ProductDetail/YAGEO/MFR-12FTF52-20K?qs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","","","","","",""
"R23","1","30K","1%, 1/6 W","","Resistor","https://www.mouser.ca/datasheet/2/447/Yageo_LR_MFR_1-1714151.pdf","YAGEO","MFR-12FTF52-30K","Mouser","603-MFR-12FTF52-30K","https://www.mouser.ca/ProductDetail/YAGEO/MFR-12FTF52-30K?qs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","","","","","",""
"R24 R29","2","160K","1%, 1/6 W","","Resistor","https://www.mouser.ca/datasheet/2/447/Yageo_LR_MFR_1-1714151.pdf","YAGEO","MFR-12FTF52-160K","Mouser","603-MFR-12FTF52-160K","https://www.mouser.ca/ProductDetail/YAGEO/MFR-12FTF52-160K?q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","","","","","",""
"R25","1","1K","5%, 1/4 W","Output limiting","Resistor","https://www.mouser.ca/datasheet/2/427/ccf07-1762725.pdf","Vishay / Dale","CCF071K00JKE36","Mouser","71-CCF071K00JKE36","https://www.mouser.ca/ProductDetail/Vishay-Dale/CCF071K00JKE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","","","","","",""
"R31","1","47K","1%, 1/6 W","*","Resistor","https://www.mouser.ca/datasheet/2/447/Yageo_LR_MFR_1-1714151.pdf","YAGEO","MFR-12FTF52-47K","Mouser","","https://www.mouser.ca/ProductDetail/YAGEO/MFR-12FTF52-47K?qs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","","","","","",""
"RV1 RV7","2","100K","LIN","","Potentiometer","https://www.mouser.ca/datasheet/2/13/alpha_taiwan_08192019_R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","Alpha","RD901F-*","Thonk","Group_Pot_Alpha_6.35mm","https://www.thonk.co.uk/shop/alpha-9mm-pots/","Mouser","311-1940F-*","https://www.mouser.ca/c/passive-components/potentiometers-tr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","SynthCube","9MMALPHAPOTMSTR","https://synthcube.com/cart/alpha-9mm-potentiometer-right-ang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"
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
